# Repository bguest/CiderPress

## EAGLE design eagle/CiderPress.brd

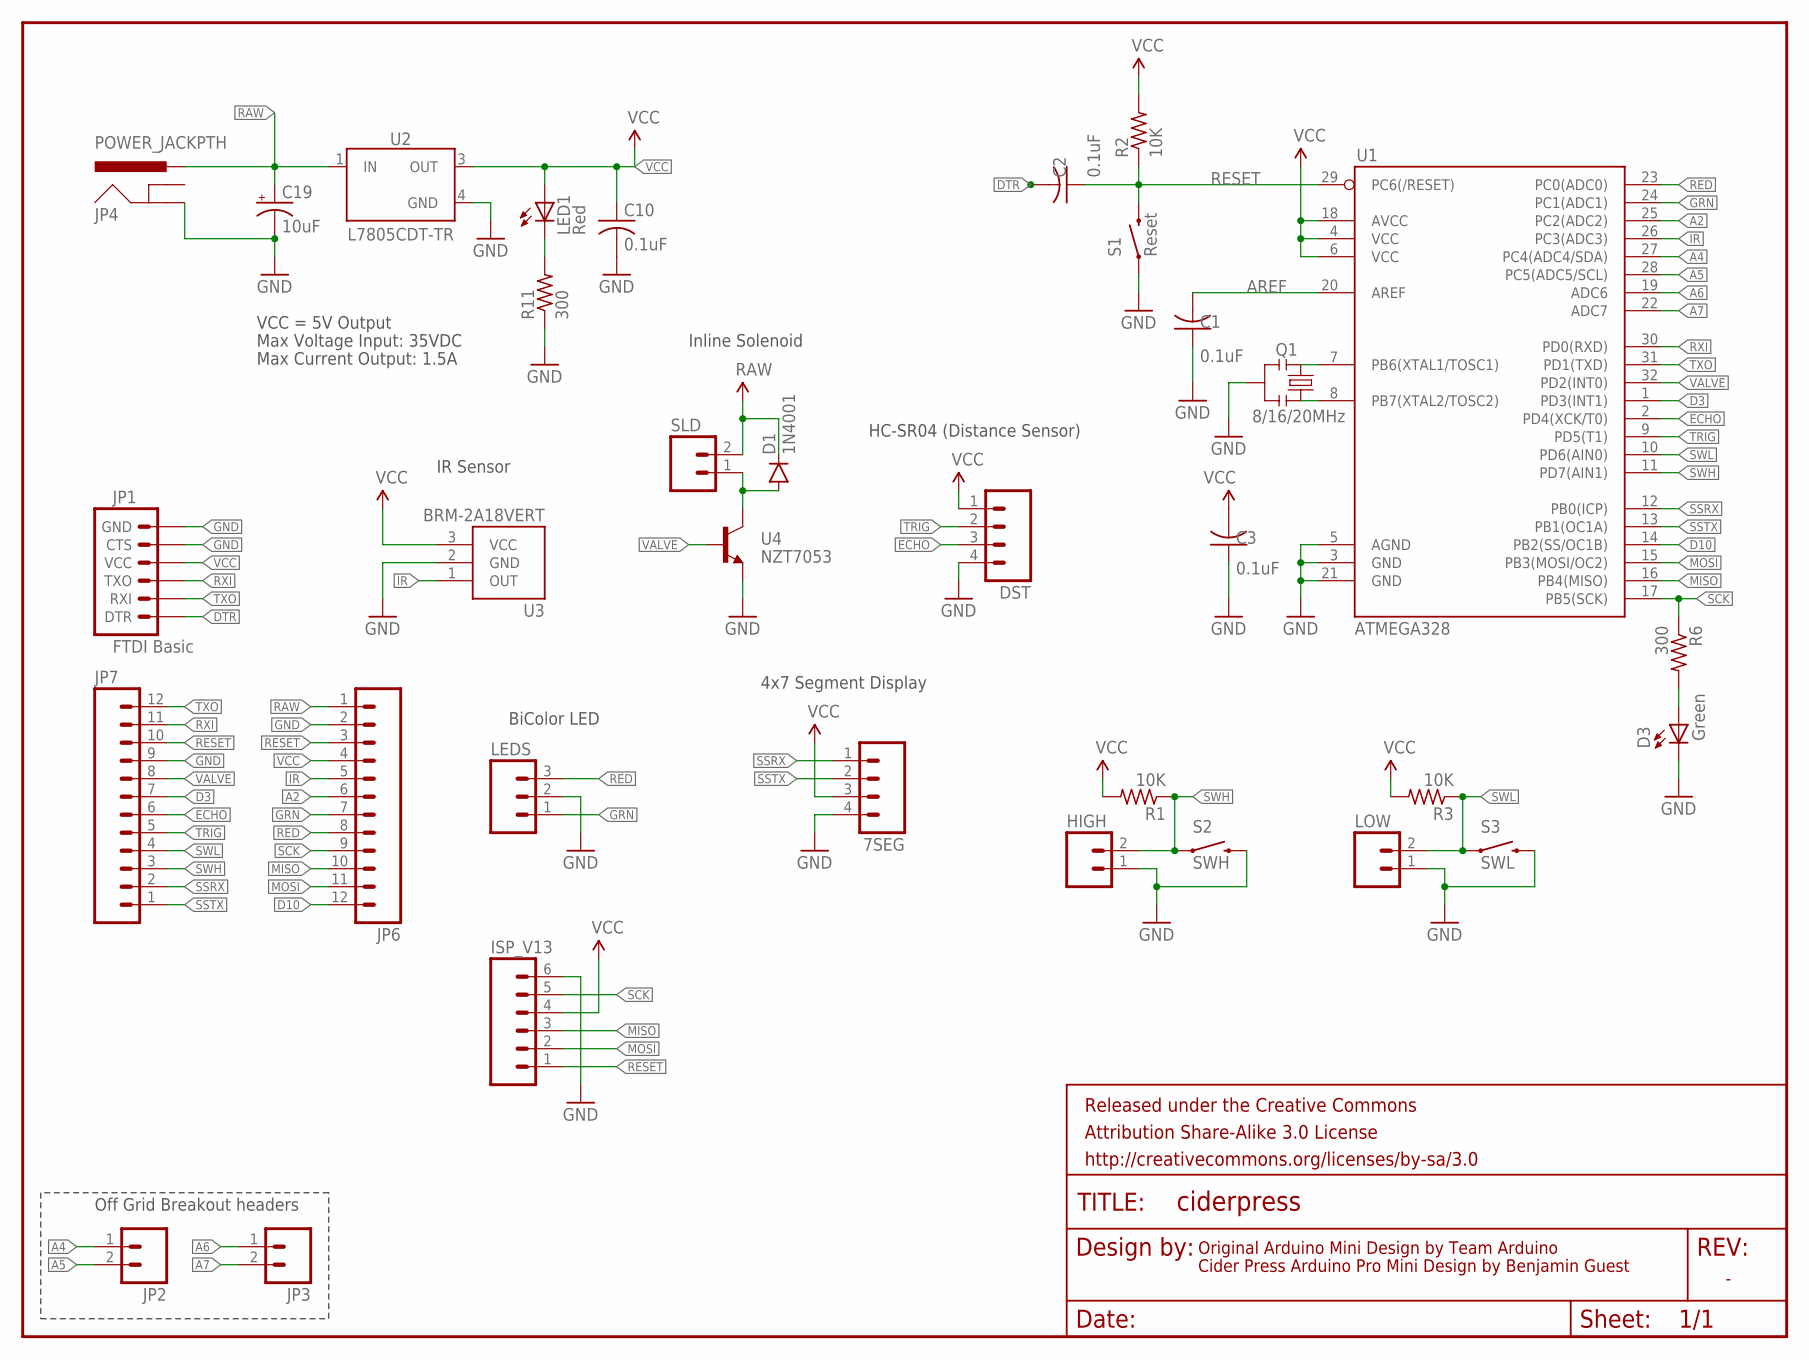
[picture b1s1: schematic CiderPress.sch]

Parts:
7SEG: M04JST-PTH; JST-4-PTH
C1, C2, C3, C10: 0.1uF; C0805
C19: 10uF; EIA3216
D1: 1N4001; DIODE-1N4001-KIT
D3: Green; CHIPLED_0805
DST: M04JST-PTH; JST-4-PTH
FRAME1: FRAME-LETTER; CREATIVE_COMMONS
HIGH: M02JST-PTH-2; JST-2-PTH
ISP_V13: M06SIP; 1X06
JP1: FTDI Basic; 1X06
JP2, JP3: M02PTH; 1X02
JP4: POWER_JACKPTH; POWER_JACK_PTH
JP6, JP7: M12PTH; 1X12
LED1: Red; CHIPLED_0805
LEDS: M03JST-PTH; JST-3-PTH
LOW: M02JST-PTH-2; JST-2-PTH
Q1: 8/16/20MHz; RESONATOR-SMD-1:1
R1, R2, R3: 10K; M0805
R6, R11: 300; M0805
S1: Reset; TACTILE-SWITCH-SMD-ALT01
S2: SWH; TACTILE-SWITCH-SMD-ALT01
S3: SWL; TACTILE-SWITCH-SMD-ALT01
SLD: M02JST-PTH-2; JST-2-PTH
U1: ATMEGA328; TQFP32-08
U2: L7805CDT-TR; DPAK
U3: BRM-2A18VERT; BRM-2508_VERT
U4: NZT7053; SOT-223

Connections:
A2: JP6.6, U1.25 (PC2(ADC2))
A4: JP2.1, U1.27 (PC4(ADC4/SDA))
A5: JP2.2, U1.28 (PC5(ADC5/SCL))
A6: JP3.1, U1.19 (ADC6)
A7: JP3.2, U1.22 (ADC7)
AREF: C1.2, U1.20 (AREF)
D3: JP7.7, U1.1 (PD3(INT1))
D10: JP6.12, U1.14 (PB2(SS/OC1B))
DTR: C2.2, JP1.1 (DTR)
ECHO: DST.3, JP7.6, U1.2 (PD4(XCK/T0))
GND: 7SEG.4, C1.1, C3.1, C10.2, C19.C (-), D3.C, DST.4, HIGH.1, ISP_V13.6, JP1.5 (CTS), JP1.6 (GND), JP4.GND, JP6.2, JP7.9, LEDS.2, LOW.1, Q1.2, R11.1, S1.1, S1.2 (1), S2.3 (2), S2.4 (2), S3.3 (2), S3.4 (2), U1.3 (GND), U1.5 (AGND), U1.21 (GND), U2.4 (GND), U3.2 (GND), U4.3 (E)
GRN: JP6.7, LEDS.1, U1.24 (PC1(ADC1))
IR: JP6.5, U1.26 (PC3(ADC3)), U3.1 (OUT)
MISO: ISP_V13.3, JP6.10, U1.16 (PB4(MISO))
MOSI: ISP_V13.2, JP6.11, U1.15 (PB3(MOSI/OC2))
unnamed: Q1.3, U1.8 (PB7(XTAL2/TOSC2))
unnamed: Q1.1, U1.7 (PB6(XTAL1/TOSC1))
unnamed: LED1.C, R11.2
unnamed: D1.A, SLD.1, U4.2 (C), U4.4 (C)
unnamed: D3.A, R6.2
RAW: C19.A (+), D1.C, JP4.PWR, JP6.1, SLD.2, U2.1 (IN)
RED: JP6.8, LEDS.3, U1.23 (PC0(ADC0))
RESET: C2.1, ISP_V13.1, JP6.3, JP7.10, R2.1, S1.3 (2), S1.4 (2), U1.29 (PC6(/RESET))
RXI: JP1.3 (TXO), JP7.11, U1.30 (PD0(RXD))
SCK: ISP_V13.5, JP6.9, R6.1, U1.17 (PB5(SCK))
SSRX: 7SEG.1, JP7.2, U1.12 (PB0(ICP))
SSTX: 7SEG.2, JP7.1, U1.13 (PB1(OC1A))
SWH: HIGH.2, JP7.3, R1.1, S2.1, S2.2 (1), U1.11 (PD7(AIN1))
SWL: JP7.4, LOW.2, R3.1, S3.1, S3.2 (1), U1.10 (PD6(AIN0))
TRIG: DST.2, JP7.5, U1.9 (PD5(T1))
TXO: JP1.2 (RXI), JP7.12, U1.31 (PD1(TXD))
VALVE: JP7.8, U1.32 (PD2(INT0)), U4.1 (B)
VCC: 7SEG.3, C3.2, C10.1, DST.1, ISP_V13.4, JP1.4 (VCC), JP6.4, LED1.A, R1.2, R2.2, R3.2, U1.4 (VCC), U1.6 (VCC), U1.18 (AVCC), U2.3 (OUT), U3.3 (VCC)

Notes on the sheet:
Original Arduino Mini Design by Team Arduino
Cider Press Arduino Pro Mini Design by Benjamin Guest
Max Voltage Input: 35VDC
Max Current Output: 1.5A
VCC = 5V Output
Off Grid Breakout headers
BiColor LED
HC-SR04 (Distance Sensor)
IR Sensor
Inline Solenoid
4x7 Segment Display

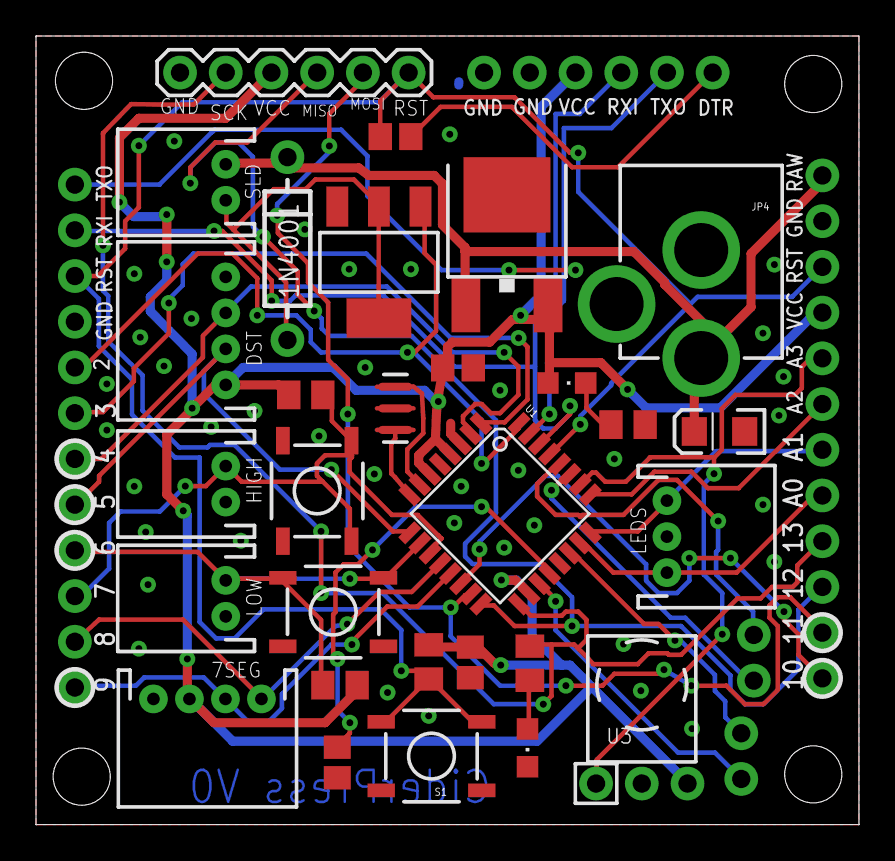
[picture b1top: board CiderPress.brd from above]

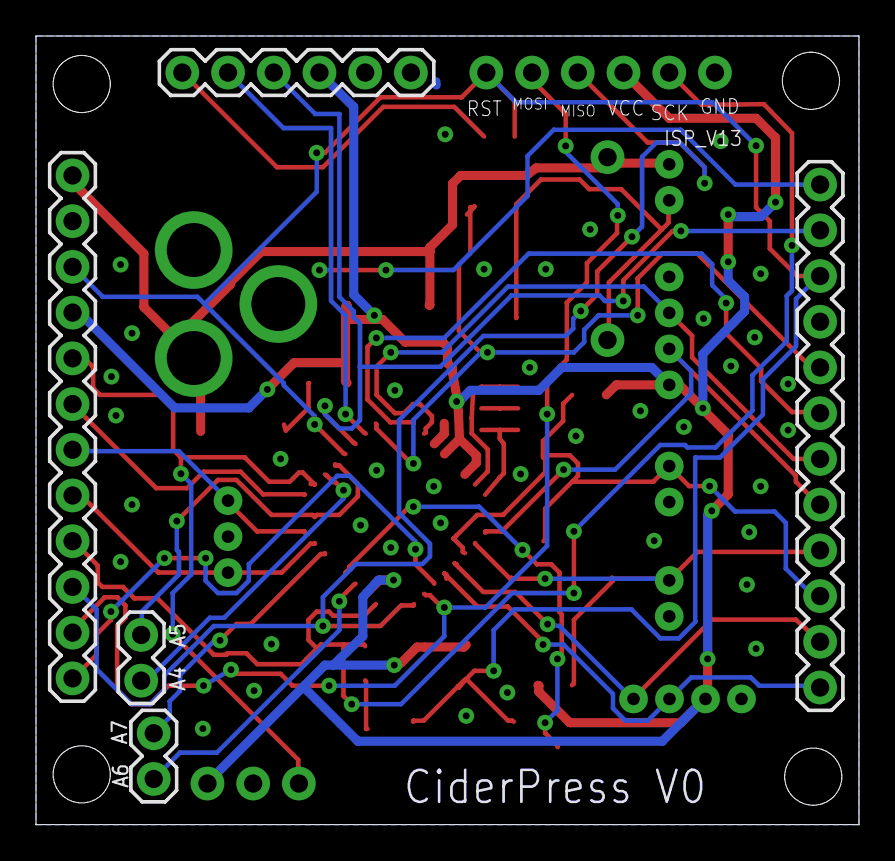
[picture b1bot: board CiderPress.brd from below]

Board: 2 copper layers, 45.7 x 43.8 mm, 35 parts (5 on the bottom side), 33 nets.

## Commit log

2015-10-31 Add Display to code
2015-10-31 Switch to using classes
2015-11-01 Add Indicator and Valve
2015-11-02 Work on Board
2015-11-03 Add codes
2015-11-05 Add IR receiver
2015-11-30 Place components
2016-01-14 Update led resistor numbers
2016-04-03 Add Different Remote

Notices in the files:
parts and their libraries:
SparkFun-Aesthetics: Licensing: CC v3.0 Share-Alike You are welcome to use this library for commercial purposes.
SparkFun-Aesthetics: Released under the Creative Commons Attribution Share-Alike 3.0 License
SparkFun-Aesthetics: http://creativecommons.org/licenses/by-sa/3.0
